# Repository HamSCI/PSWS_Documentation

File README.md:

# PSWS_Documentation
Documentation for the HamSCI Personal Space Weather Station Project

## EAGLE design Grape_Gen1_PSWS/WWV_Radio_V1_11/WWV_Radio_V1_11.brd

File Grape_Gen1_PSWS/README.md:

# PSWS_Documentation
Documentation for the HamSCI Personal Space Weather Station Project

This documentation is licensed with the Attribution-ShareAlike 4.0 International license https://creativecommons.org/licenses/by-sa/4.0/legalcode.

## First releaase - FLDIGI-4.1.09
- Basee on a modified version of FLDIGI-4.1.09
- File structure based oof of /home/pi/WWVdata/...

## Second release - FLDIGI-4.1.13
- based on modified version of FLDIGI 4.1.13
- file structure based off of /home/pi/PSWS/...
- bashrc (stored as .bashrc in home directory) added with new aliases

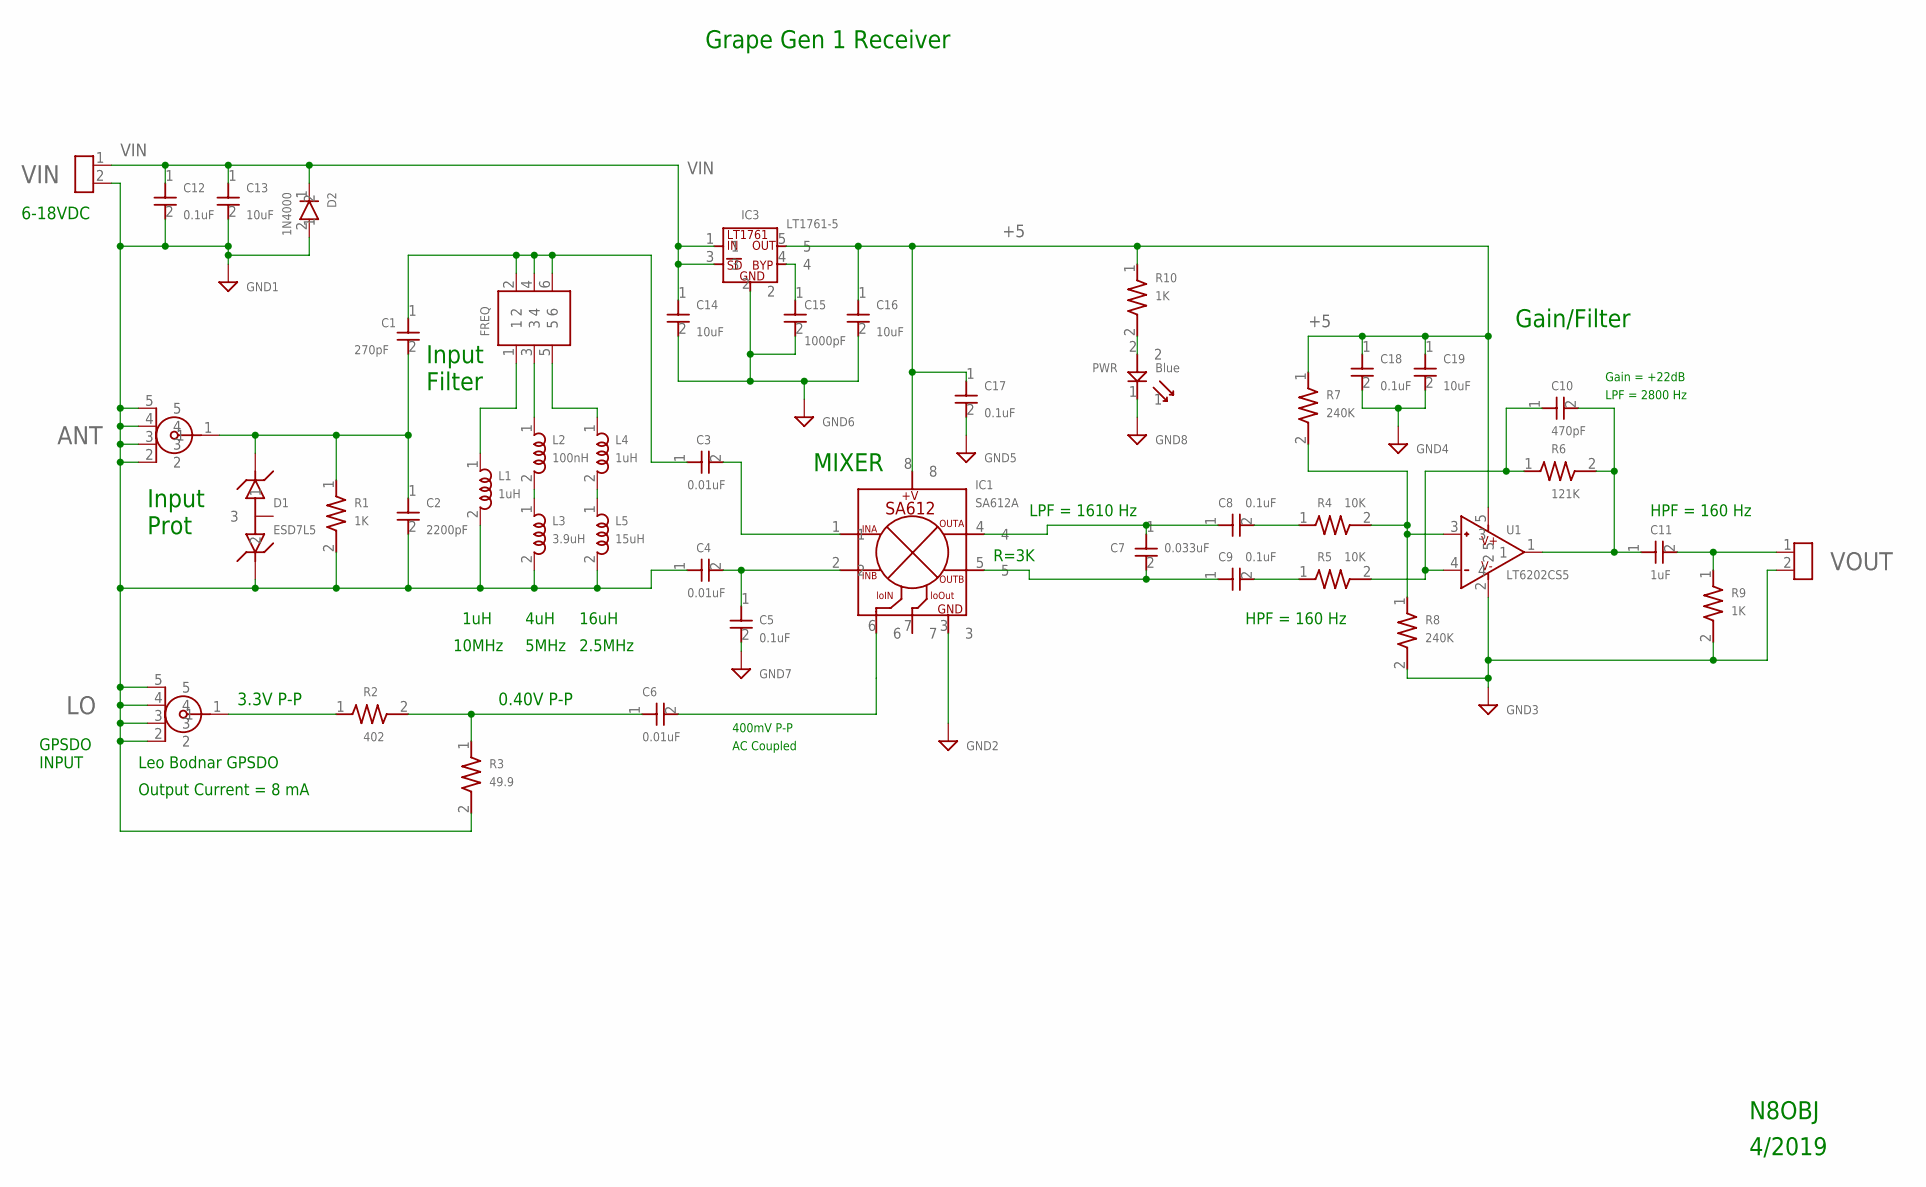
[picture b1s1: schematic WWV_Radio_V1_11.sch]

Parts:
ANT: SMAEDGEPCB
C1: 270pF; C0805
C2: 2200pF; C0805
C3, C4, C6: 0.01uF; C0805
C5, C8, C9, C12, C17, C18: 0.1uF; C0805
C7: 0.033uF; C0805
C10: 470pF; C0805
C11: 1uF; C0805
C13, C14, C16, C19: 10uF; C0805
C15: 1000pF; C0805
D1: ESD7L5; ESD7L
D2: 1N4000; 1N4000_PTH
FREQ: 2X3PINHEADER
IC1: SA612A; SO08
IC3: LT1761-5; TSOT-23
L1, L4: 1uH; R1206
L2: 100nH; R1206
L3: 3.9uH; R1206
L5: 15uH; R1206
LO: SMAEDGEPCB
PWR: Blue; LED0805
R1, R9, R10: 1K; R0805
R2: 402; R0805
R3: 49.9; R0805
R4, R5: 10K; R0805
R6: 121K; R0805
R7, R8: 240K; R0805
U1: LT6202CS5; SOT23_5
VIN: 2PINBERG
VOUT: 2PINBERG

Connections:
+5: C16.1, C17.1, C18.1, C19.1, IC1.8, IC3.5, R7.1, R10.1, U1.5
GND: ANT.2, ANT.3, ANT.4, ANT.5, C2.2, C4.1, C5.2, C12.2, C13.2, C14.2, C15.2, C16.2, C17.2, C18.2, C19.2, D1.2, D2.2, IC1.3, IC3.2, L1.2, L3.2, L5.2, LO.2, LO.3, LO.4, LO.5, PWR.1, R1.2, R3.2, R8.2, R9.2, U1.2, VIN.2, VOUT.2
unnamed: C10.1, R5.2, R6.1, U1.4
unnamed: R4.2, R7.2, R8.1, U1.3
unnamed: LO.1, R2.1
unnamed: C8.2, R4.1
unnamed: ANT.1, C1.2, C2.1, D1.1, R1.1
unnamed: L4.2, L5.1
unnamed: C4.2, C5.1, IC1.2
unnamed: C7.1, C8.1, IC1.4
unnamed: C7.2, C9.1, IC1.5
unnamed: C6.1, R2.2, R3.1
unnamed: C10.2, C11.1, R6.2, U1.1
unnamed: C15.1, IC3.4
unnamed: C9.2, R5.1
unnamed: C3.2, IC1.1
unnamed: C1.1, C3.1, FREQ.2, FREQ.4, FREQ.6
unnamed: L2.2, L3.1
unnamed: C11.2, R9.1, VOUT.1
unnamed: PWR.2, R10.2
unnamed: FREQ.1, L1.1
unnamed: FREQ.3, L2.1
unnamed: FREQ.5, L4.1
unnamed: C6.2, IC1.6
VIN: C12.1, C13.1, C14.1, D2.1, IC3.1, IC3.3, VIN.1

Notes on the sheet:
MIXER
Input
Gain = +22dB
LPF = 2800 Hz
400mV P-P
AC Coupled
HPF = 160 Hz
LPF = 1610 Hz
R=3K
GPSDO
INPUT
1uH
4uH
16uH
10MHz
5MHz
2.5MHz
Leo Bodnar GPSDO
Output Current = 8 mA
6-18VDC
3.3V P-P
0.40V P-P
Grape Gen 1 Receiver
N8OBJ
4/2019
Filter
Gain/Filter
Prot

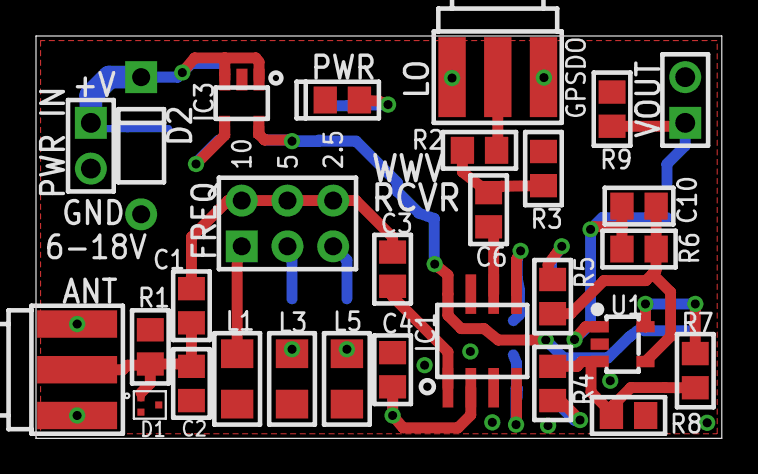
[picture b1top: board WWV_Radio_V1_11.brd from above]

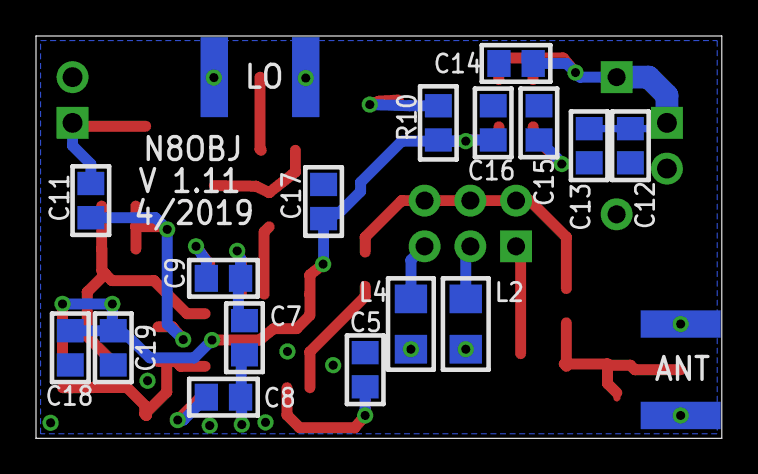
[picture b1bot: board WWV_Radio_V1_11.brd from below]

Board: 2 copper layers, 38.1 x 22.4 mm, 45 parts (16 on the bottom side), 25 nets.

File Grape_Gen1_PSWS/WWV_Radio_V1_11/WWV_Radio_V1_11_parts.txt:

Partlist exported from WWV_Radio_V1_11.sch			N8OBJ 4/2019

This parts list is available on Digi-Key for ordering under WWV_Grape1

Qty Value        Device       Parts                    	DigiKey Part #

6   0.1uF        C0805        C5, C8, C9, C12, C17, C18	399-8000-1-ND
3   0.01uF       C0805        C3, C4, C6      		399-17616-1-ND
1   0.033uF	 C0805	      C7       			732-8077-1-ND
1   1uF          C0805        C11                      	732-7678-1-ND
4   10uF         C0805        C13, C14, C16, C19   	445-5985-1-ND
1   270pF        C0805        C1                       	478-1364-1-ND
1   470pF        C0805        C10                      	732-8066-1-ND
1   1000pF       C0805        C15                      	732-8068-1-ND
1   2200pF       C0805        C2                       	732-8070-1-ND
1   49.9         R0805        R3                       	P49.9CCT-ND
1   402          R0805        R2                       	P402CCT-ND
3   1K           R0805        R1, R9, R10   		P1.00KCCT-ND
2   10K          R0805        R4, R5                   	311-10KARCT-ND
1   121K         R0805        R6                       	541-121KCCT-ND
2   240K         R0805        R7, R8                   	541-240KCCT-ND
1   1N4000       1N4000_PTH   D2           		1N4001RLGOSCT-ND
1   ESD7L5       ESD7L        D1                      	ESD7L5.0DT5GOSCT-ND       
2   1uH          L1206        L1, L4                   	490-6604-1-ND
1   3.9uH        L1206        L3                       	490-16851-1-ND
1   15uH         L1206        L5                       	490-11672-1-ND
1   100nH        L1206        L2                       	490-12091-1-ND
1   Blue LED     LED0805      PWR                	754-2118-1-ND
1   LT1761-5     LT1761-X     IC3                    	LT1761IS5-5#TRMPBFCT-ND
1   LT6202CS5    LT6202CS5    U1                	LT6202CS5#TRMPBFCT-ND
1   SA612A       SA612A       IC1			568-5045-1-ND
2   SMA Edge     SMAEDGEPCB   ANT, LO  			CON-SMA-EDGE-S-ND            
2   2PINBERG     2PINBERG     VIN, VOUT  		3M156306-02-ND [DO NOT USE]
1   2X3PINHEADER 2X3PINHEADER FREQ   			609-3234-ND
1   JMPR	 JMPR	      JMP1			S9337-ND

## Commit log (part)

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2020-08-02 First release software anad all sources
2020-08-02 updates to original rease - support files and docs
2020-08-02 Added version 2 of FLDIGI mods (FLDIGI-4.1.13) Utilities and support files
2020-08-02 updated readme.md file to reflect additions
2020-08-02 Added readme.md for 2nd software release
2020-08-02 removed older duplicated files
2020-08-12 fixed spelling error
2020-08-28 updated files
2020-10-17 Added internal pics of Leo Bodnar GPSDO
2020-11-22 Added feature to turn on/off autoplot of day's data
2020-11-22 Update WWV_plt2.py
    Removed test file case as being default file (oops!)
2020-12-04 Updated Grape Gen 1 python code and .bashrc file for operation of station
2020-12-05 moved PSWSsetup.py to home dir - needed for initial run. DOH!
2020-12-05 Added PSWSsetup.py seperate directory for history of revisions capture
2020-12-05 added documentaion readme.md for clairity
2020-12-10 added install procedure for maidenhead python okg needed to run PSWSsetup.py script
2020-12-15 Added python script to read metadata. Added filespec and Grape operation document (all revs)
2020-12-15 pushed filespec doc into more appropriately named directory
2020-12-16 added verbage for PSWSinfo.py program usage and intent
2021-01-04 added freq change algorithm for Grape PSWS Gen 1
2021-01-29 Updated spec for Sxfer addition, more verbage in daily operation of a Grafpe Gen 1
2021-01-31 fixed edit history mistake....
2021-02-01 fixed Srawdata typo
2021-02-14 Added uSD card image reduction code
2021-03-02 Added PCB layout, parts list, block diag for Grape Gen 1 Receiver
2021-03-02 Missed adding block diagram for Grape Gen 1 Receier
2021-03-05 Added Grape Gen 1 supplies Ordering List
2021-03-16 Added more docs for easier build process
2021-03-16 Update to docs for easier build process for users
2021-03-30 changed ref designator char spacing from - to + for less confusion
2021-06-06 Files added to describe creation of OS image and Grape Gen 1 PSWS setup
2021-06-08 house cleaning
2022-01-26 Added support for Smagtmp directory in file structure
2022-01-26 Added support for Magnetometer & Temperature data in PSWS/ filesystem
2022-02-12 Added autoxfer files pushed out to users on 2/10/2022
2022-03-07 cleaning up old files
2023-05-10 adding sending node info to me
2023-05-10 updates and typo fixes
2025-07-22 Create LICENSE
2025-07-22 empty docs
2025-07-22 add readthedocs.yml
2025-07-22 change theme
2025-07-22 added requirement
2025-07-22 use requirements.txt
2025-07-22 add wsprdaemon install page
2025-07-22 trying things
2025-07-22 fix underscore
2025-07-22 add rtd badge
2025-07-22 convert to rst
2025-07-22 add watch.sh
